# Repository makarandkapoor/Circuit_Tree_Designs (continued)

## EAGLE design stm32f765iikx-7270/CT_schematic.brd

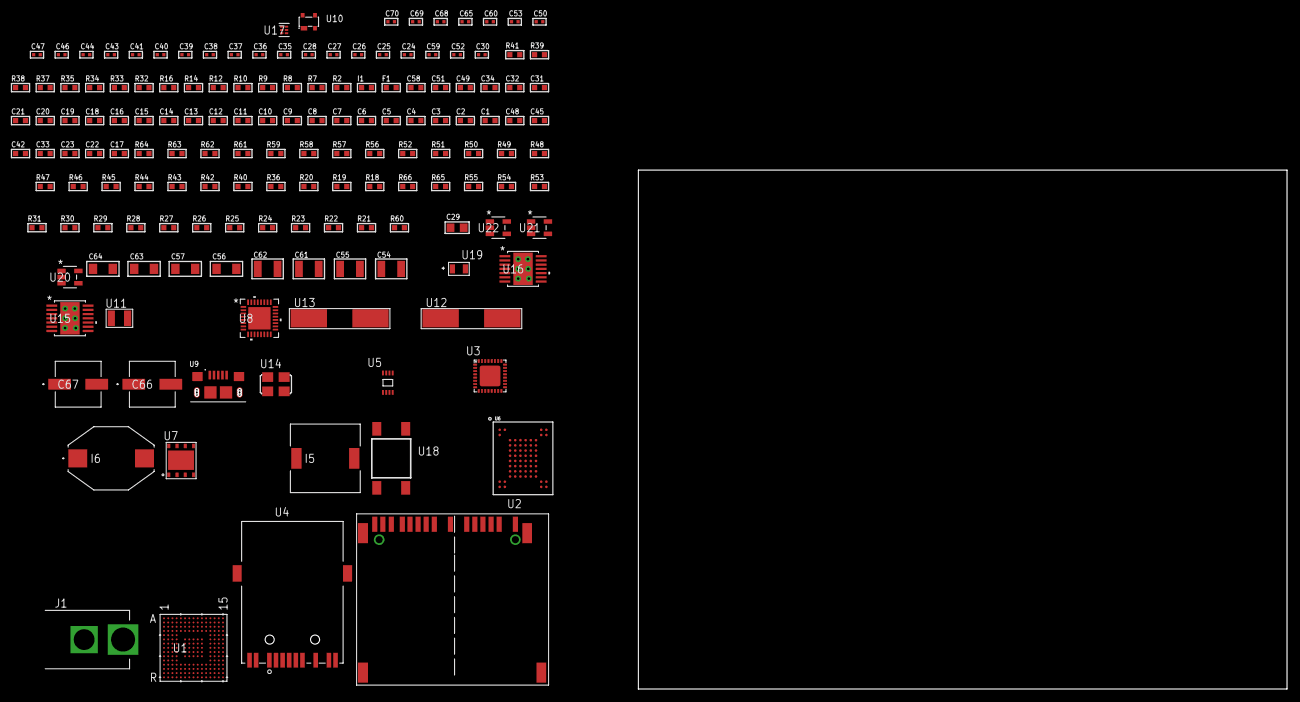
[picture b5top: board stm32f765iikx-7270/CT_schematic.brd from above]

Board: 2 copper layers, 154 parts (0 on the bottom side), 120 nets, no tracks yet.

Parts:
C1, C19, C31, C32, C34, C49, C51, C58: 1e-06; C0603
C2, C3, C4, C5, C6, C7, C8, C9, C10, C11, C12, C13, C14, C15, C16, C20, C21: 1e-07; C0603
C17: 4.7e-06; C0603
C18: 1e-08; C0603
C22, C23, C42, C45, C48: 2.2e-06; C0603
C24, C25, C26, C27, C35, C36: 1e-11; C0402
C28, C38, C39, C40, C41, C43, C44, C46, C47, C53, C60, C65: 1e-07; C0402
C29: 1e-05; C0805
C30: 2.2e-08; C0402
C33: 4.7e-10; C0603
C37, C50, C68, C69, C70: 1e-08; C0402
C52, C59: 3.3e-09; C0402
C54, C55, C61, C62: 2.2e-05; C1210
C56, C57, C63, C64: 1e-05; C1206
C66, C67: 0.0001; EXV-9H
F1: 240.0; L0603
I1: 97.0; R0603
I5: 3.8e-06; DR1040
I6: 1e-05; IND_PM3316
J1: PJ-037B; PJ-037B_PACKAGE
R2: 1000.0; R0603
R7, R8, R9: 4700.0; R0603
R10, R12, R14, R16: 2200.0; R0603
R18, R19, R20, R40, R42, R43, R44, R45, R46, R47, R48, R49, R50, R51, R52, R56, R57, R62, R63: 10000.0; R0603
R21, R22, R23, R24, R25, R26, R27, R28, R29, R30, R31, R53, R54, R55: 100000.0; R0603
R32, R33: 0.1; R0603
R34, R35: 200.0; R0603
R36: 12100.0; R0603
R37, R38, R39, R41: 49.9; R0603
R58: 30000.0; R0603
R59, R61: 22000.0; R0603
R60: 71007.101651032; R0603
R64: 82000.0; R0603
R65: 300000.0; R0603
R66: 120000.0; R0603
U1: STM32F765IIK6; UFBGA176_25
U2: 10100565
U3: LAN8710AI-EZK; QFN-32
U4: 7498011122R
U5: 24AA00T-I/MNY; TDFN-8/6MM
U6: mt29f4g08abbdah4; VFBGA-63
U7: SST26WF016B-104I/MF; WFDN-8
U8: TUSB1210BRHBR; RHB32_3P45X3P45
U9: 10118193-0001LF; FCI_10118193-0001LF
U10: prtr5v0u2ax; SOT143B
U11: ABS07-32.768KHZ-7-T
U12, U13: ABLS-25.000MHZ-B2F-T
U14: ASFL1-26MHZ-NCS; ASFL1
U15: tps54325PWP; HTSSOP14
U16: tps54225PWP; HTSSOP14
U17: TPS3895ADRYR; SON-6
U18: 4-1437565-2; SW_4-1437565-2
U19: Q65110A2395; LGM67K-G1J2-24-Z
U20, U21, U22: nc7sz125m5x; NC7SZ125M5X

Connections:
CLK_CRYSTAL_U1_E1: C24.1, U1.E1, U11.1
CLK_CRYSTAL_U1_F1: C25.1, U1.F1, U11.2
CLK_CRYSTAL_U1_G1: C26.1, U1.G1, U12.1
CLK_CRYSTAL_U1_H1: C27.1, U1.H1, U12.2
CLK_CRYSTAL_U3_4: C36.1, U3.4, U13.2
CLK_CRYSTAL_U3_5: C35.1, U3.5, U13.1
CLK_U8_1: U8.1, U14.3
GND: C1.2, C2.2, C3.2, C4.2, C5.2, C6.2, C7.2, C8.2, C9.2, C10.2, C11.2, C12.2, C13.2, C14.2, C15.2, C16.2, C17.2, C18.2, C19.2, C20.2, C21.2, C22.2, C23.2, C24.2, C25.2, C26.2, C27.2, C28.2, C29.2, C30.2, C31.2, C32.2, C33.2, C34.2, C35.2, C36.2, C37.2, C38.2, C39.2, C40.2, C41.2, C42.2, C43.2, C44.2, C45.2, C46.2, C47.2, C48.2, C49.2, C50.2, C51.2, C52.2, C54.2, C55.2, C56.2, C57.2, C58.2, C59.2, C61.2, C62.2, C63.2, C64.2, C65.2, C66.2, C67.2, C68.2, C69.2, C70.2, J1.2, R2.2, R18.2, R20.2, R32.2, R33.2, R34.2, R36.2, R47.2, R59.2, R61.2, R64.2, R66.2, U1.D5, U1.D7, U1.D8, U1.D9, U1.F2, U1.F6, U1.F7, U1.F8, U1.F9, U1.F10, U1.F12, U1.G2, U1.G6, U1.G7, U1.G8, U1.G9, U1.G10, U1.G12, U1.H6, U1.H7, U1.H8, U1.H9, U1.H10, U1.H12, U1.J6, U1.J7, U1.J8, U1.J9, U1.J10, U1.K6, U1.K7, U1.K8, U1.K9, U1.K10, U1.M1, U1.M8, U1.M9, U1.N1, U2.6, U2.10, U2.12, U2.16, U2.17, U2.20, U2.21, U3.EXP, U4.10, U5.4, U6.C5, U6.F7, U6.K3, U6.K8, U7.4, U7.9, U8.33, U9.5, U9.6, U9.7, U9.8, U9.9, U10.1, U14.2, U15.5, U15.8, U15.9, U15.15, U16.5, U16.8, U16.9, U16.15, U17.2, U19.C, U20.1, U20.3, U21.1, U21.3, U22.1, U22.3
NET_U1_C6: R19.1, U1.C6
NET_U1_D6: R18.1, U1.D6
NET_U1_E2: R12.1, U1.E2, U5.5
NET_U1_F13: C23.1, U1.F13
NET_U1_H3: R10.1, U1.H3, U5.6
NET_U1_J1: R8.1, U1.J1, U21.4
NET_U1_L4: R20.1, U1.L4
NET_U1_M3: R14.1, U1.M3, U3.17
NET_U1_M10: C22.1, U1.M10
NET_U1_P2: R16.1, U1.P2, U3.16
NET_U1_R1: C18.1, C19.1, F1.1, U1.P1, U1.R1
NET_U1_R15: U18.3, U18.4
NET_U2_1: R23.1, U2.1
NET_U2_2: R22.1, U2.2
NET_U2_18: U2.18, U2.19
NET_U3_1: C31.1, I1.1, R37.2, R38.2, R39.2, R41.2, U3.1, U3.27
NET_U3_6: C32.1, C33.1, U3.6
NET_U3_18: R40.1, U3.18
NET_U3_19: R7.1, U3.19, U20.4
NET_U3_32: R36.1, U3.32
NET_U4_1: R37.1, U3.29, U4.1
NET_U4_3: R35.2, R38.1, U3.28, U4.3
NET_U4_4: R39.1, U3.31, U4.4
NET_U4_5: C30.1, U4.2, U4.5
NET_U4_6: R41.1, U3.30, U4.6
NET_U4_8: R33.1, U4.8
NET_U4_9: R35.1, U4.9
NET_U4_11: U3.2, U4.11
NET_U4_12: R34.1, U4.12
NET_U4_13: R32.1, U4.13, U4.14
NET_U6_C3: R52.1, U6.C3
NET_U8_11: R56.1, U8.11
NET_U8_12: C48.1, U8.12
NET_U8_14: R57.1, U8.14
NET_U8_20: C45.1, U8.20
NET_U8_27: R9.1, U8.27, U22.4
NET_U9_1: C49.1, U8.22, U9.1, U10.4
NET_U9_2: U8.19, U9.2, U10.3
NET_U9_3: U8.18, U9.3, U10.2
NET_U15_2: R58.2, R59.1, U15.2
NET_U15_3: C51.1, U15.3
NET_U15_4: C52.1, U15.4
NET_U15_10: C53.1, I5.1, U15.10, U15.11
NET_U15_12: C53.2, U15.12
NET_U16_2: R60.2, R61.1, U16.2
NET_U16_3: C58.1, U16.3
NET_U16_4: C59.1, U16.4
NET_U16_10: C60.1, I6.1, U16.10, U16.11
NET_U16_12: C60.2, U16.12
NET_U17_1: R63.1, R64.1, U17.1
NET_U17_3: R65.2, R66.1, U17.3
NET_U17_4: R62.1, U17.4, U20.2, U21.2, U22.2
NET_U18_1: R2.1, U18.1, U18.2
PROC_ETH_COL: R44.1, U1.G4, U3.15
PROC_ETH_CRS: U1.F4, U3.14
PROC_ETH_RXD0: R42.1, U1.N5, U3.11
PROC_ETH_RXD1: R43.1, U1.P5, U3.10
PROC_ETH_RXD2: U1.M11, U3.9
PROC_ETH_RXD3: R47.1, U1.N12, U3.8
PROC_ETH_RX_CLK: R46.1, U1.N2, U3.7
PROC_ETH_RX_DV: U1.R3, U3.26
PROC_ETH_RX_ER: R45.1, U1.E3, U3.13
PROC_ETH_TXD0: U1.A8, U3.22
PROC_ETH_TXD1: U1.A7, U3.23
PROC_ETH_TXD2: U1.M4, U3.24
PROC_ETH_TXD3: U1.A2, U3.25
PROC_ETH_TX_CLK: U1.M5, U3.20
PROC_ETH_TX_EN: U1.B9, U3.21
PROC_FMC_A16: U1.N14, U6.D5
PROC_FMC_A17: U1.N13, U6.C4
PROC_FMC_D0: U1.M14, U6.H4
PROC_FMC_D1: U1.L14, U6.J4
PROC_FMC_D2: U1.B12, U6.K4
PROC_FMC_D3: U1.C12, U6.K5
PROC_FMC_D4: U1.R8, U6.K6
PROC_FMC_D5: U1.P8, U6.J7
PROC_FMC_D6: U1.P9, U6.K7
PROC_FMC_D7: U1.R9, U6.J8
PROC_FMC_INT: R48.1, U1.J14, U6.C8
PROC_FMC_NCE: R49.1, U1.C10, U6.C6
PROC_FMC_NOE: R51.1, U1.D10, U6.D4
PROC_FMC_NWE: R50.1, U1.C11, U6.C7
PROC_QUADSPI_BK1_IO0: U1.L3, U7.5
PROC_QUADSPI_BK1_IO1: U1.L2, U7.2
PROC_QUADSPI_BK1_IO2: R54.1, U1.K1, U7.3
PROC_QUADSPI_BK1_IO3: R55.1, U1.K2, U7.7
PROC_QUADSPI_BK1_NCS: R53.1, U1.B6, U7.1
PROC_QUADSPI_CLK: U1.L1, U7.6
PROC_SDMMC1_CK: R21.1, U1.A12, U2.8
PROC_SDMMC1_D0: R24.1, U1.G14, U2.4
PROC_SDMMC1_D1: R25.1, U1.F14, U2.3
PROC_SDMMC1_D2: R26.1, U1.B14, U2.15
PROC_SDMMC1_D3: R27.1, U1.B13, U2.14
PROC_SDMMC1_D4: R28.1, U1.A5, U2.13
PROC_SDMMC1_D5: R29.1, U1.B4, U2.11
PROC_SDMMC1_D6: R30.1, U1.H15, U2.7
PROC_SDMMC1_D7: R31.1, U1.G15, U2.5
PROC_USB_OTG_HS_ULPI_CK: U1.P4, U8.26
PROC_USB_OTG_HS_ULPI_D0: U1.R2, U8.3
PROC_USB_OTG_HS_ULPI_D1: U1.R5, U8.4
PROC_USB_OTG_HS_ULPI_D2: U1.R4, U8.5
PROC_USB_OTG_HS_ULPI_D3: U1.R12, U8.6
PROC_USB_OTG_HS_ULPI_D4: U1.R13, U8.7
PROC_USB_OTG_HS_ULPI_D5: U1.P12, U8.9
PROC_USB_OTG_HS_ULPI_D6: U1.P13, U8.10
PROC_USB_OTG_HS_ULPI_D7: U1.A6, U8.13
PROC_USB_OTG_HS_ULPI_DIR: U1.E4, U8.31
PROC_USB_OTG_HS_ULPI_NXT: U1.H4, U8.2
PROC_USB_OTG_HS_ULPI_STP: U1.M2, U8.29
VCC_S1_15V2: C56.1, C57.1, C63.1, C64.1, C66.1, C67.1, J1.1, U15.7, U15.13, U15.14, U16.7, U16.13, U16.14
VCC_TIER1_1V8: C1.1, C2.1, C3.1, C4.1, C5.1, C6.1, C7.1, C8.1, C9.1, C10.1, C11.1, C12.1, C13.1, C14.1, C15.1, C16.1, C17.1, C21.1, C28.1, C29.1, C34.1, C37.1, C38.1, C39.1, C40.1, C41.1, C42.1, C43.1, C46.1, C47.1, C54.1, C55.1, C65.1, C68.1, C69.1, C70.1, F1.2, I5.2, R7.2, R8.2, R9.2, R10.2, R12.2, R14.2, R16.2, R19.2, R21.2, R22.2, R23.2, R24.2, R25.2, R26.2, R27.2, R28.2, R29.2, R30.2, R31.2, R40.2, R42.2, R43.2, R44.2, R45.2, R46.2, R48.2, R49.2, R50.2, R51.2, R52.2, R53.2, R54.2, R55.2, R56.2, R57.2, R58.1, R62.2, R63.2, R65.1, U1.C1, U1.C5, U1.C7, U1.C8, U1.C9, U1.F3, U1.G3, U1.G13, U1.J12, U1.J13, U1.K4, U1.N8, U1.N9, U1.N10, U2.9, U3.12, U5.8, U6.D3, U6.G4, U6.H8, U6.J6, U7.8, U8.28, U8.30, U8.32, U15.1, U17.6, U20.5, U21.5, U22.5
VCC_TIER1_3V3: C20.1, C44.1, C50.1, C61.1, C62.1, I1.2, I6.2, R60.1, U1.H13, U8.21, U14.4, U16.1

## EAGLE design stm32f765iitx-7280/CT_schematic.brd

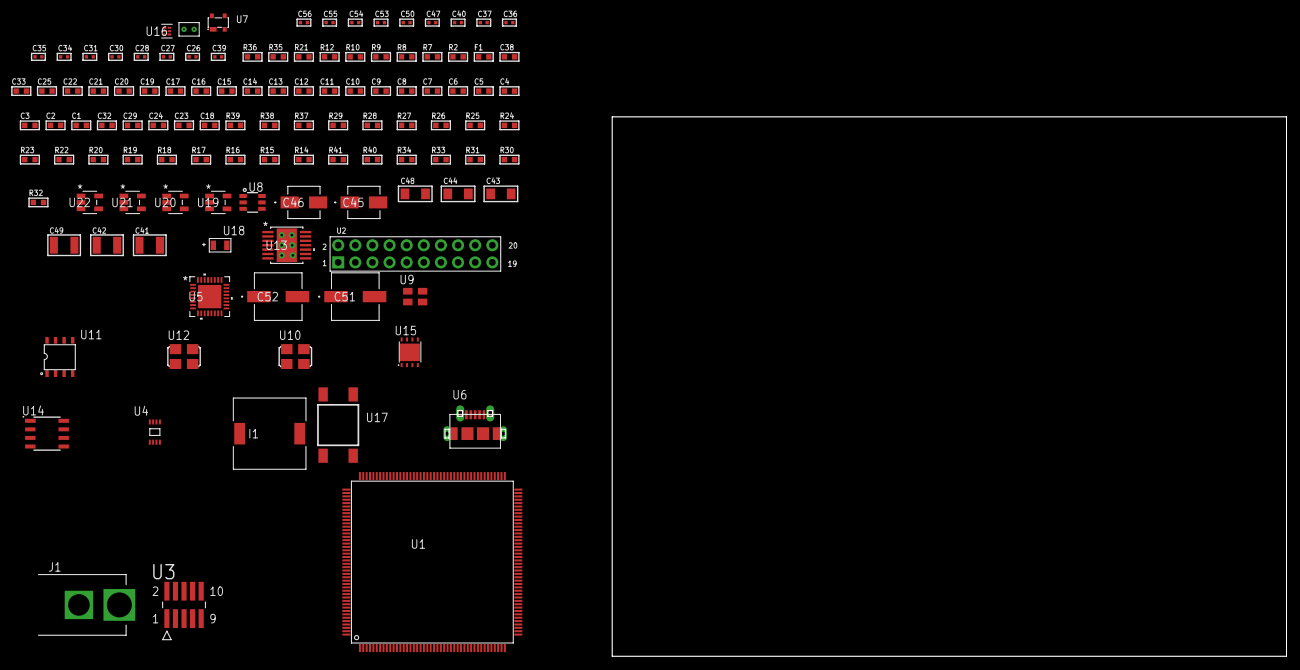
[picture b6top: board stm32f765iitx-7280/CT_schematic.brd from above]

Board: 2 copper layers, 124.8 x 80.0 mm, 116 parts (0 on the bottom side), 57 nets, no tracks yet.

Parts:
C1, C20, C25, C33, C38: 1e-06; C0603
C2, C3, C4, C5, C6, C7, C8, C9, C10, C11, C12, C13, C14, C15, C16, C17, C21, C22: 1e-07; C0603
C18: 4.7e-06; C0603
C19: 1e-08; C0603
C23, C24, C29, C32: 2.2e-06; C0603
C26, C28, C30, C31, C40, C50: 1e-07; C0402
C27, C34, C35, C36, C37, C47, C53, C54, C55, C56: 1e-08; C0402
C39: 3.3e-09; C0402
C41, C42: 2.2e-05; C1210
C43, C44, C48: 1e-05; C1206
C45: 1e-06; EXV-9B
C46: 2.2e-06; EXV-9B
C49: 1e-05; C1210
C51, C52: 0.0001; EXV-9H
F1: 240.0; L0603
I1: 5.2e-06; DR1040
J1: PJ-037B; PJ-037B_PACKAGE
R2, R36: 1000.0; R0603
R7, R8, R9: 4700.0; R0603
R10, R12: 2200.0; R0603
R14, R15, R16, R17, R18, R19, R20, R22, R23, R24, R26, R27, R37, R38: 10000.0; R0603
R21: 5.0; R0603
R25: 47000.0; R0603
R28: 30000.0; R0603
R29: 22000.0; R0603
R30, R31, R33, R34: 100000.0; R0603
R32: 164658.62; R0603
R35: 3900.0; R0603
R39: 82000.0; R0603
R40: 300000.0; R0603
R41: 120000.0; R0603
U1: STM32F765IIT6; LQFP176
U2: arducam_ov2640; ARDUCAM
U3: FTSH-105-01-L-DV-K; SAMTEC_FTSH-105-01-L-DV-K
U4: 24AA128T-I/MNY; TDFN-8/6MM
U5: TUSB1210BRHBR; RHB32_3P45X3P45
U6: 47590-0001; MICRO_USB_AB
U7: prtr5v0u2ax; SOT143B
U8: MAX4995AAUT+T; SOT-23-6
U9: ASEK-32.768KHz-ECST; ASEK
U10: ASFL1-25MHZ-NCS; ASFL1
U11: idt74fct38072; IDT74FCT38072
U12: ASFL1-26MHZ-NCS; ASFL1
U13: tps54225PWP; HTSSOP14
U14: LP2954AIMX/NOPB; LP2954
U15: LP3878SDX-ADJ/NOPB; WSON-8
U16: TPS3895ADRYR; SON-6
U17: 4-1437565-2; SW_4-1437565-2
U18: Q65110A2395; LGM67K-G1J2-24-Z
U19, U20, U21, U22: nc7sz125m5x; NC7SZ125M5X
U23: Dummy; DUMMY_PACKAGE_251

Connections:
CLK_U1_9: U1.9, U9.3
CLK_U1_29: U1.29, U11.6
CLK_U2_8: U2.8, U11.7
CLK_U5_1: U5.1, U12.3
CLK_U11_3: U10.3, U11.3
GND: C1.2, C2.2, C3.2, C4.2, C5.2, C6.2, C7.2, C8.2, C9.2, C10.2, C11.2, C12.2, C13.2, C14.2, C15.2, C16.2, C17.2, C18.2, C19.2, C20.2, C21.2, C22.2, C23.2, C24.2, C25.2, C26.2, C27.2, C28.2, C29.2, C30.2, C31.2, C32.2, C33.2, C34.2, C35.2, C36.2, C37.2, C38.2, C39.2, C41.2, C42.2, C43.2, C44.2, C45.2, C46.2, C47.2, C48.2, C49.2, C50.2, C51.2, C52.2, C53.2, C54.2, C55.2, C56.2, J1.2, R2.2, R14.2, R16.2, R20.2, R21.2, R22.2, R23.2, R25.2, R29.2, R33.2, R36.2, R39.2, R41.2, U1.14, U1.22, U1.37, U1.61, U1.71, U1.90, U1.102, U1.113, U1.126, U1.135, U1.148, U1.158, U2.2, U2.20, U3.3, U3.5, U4.4, U4.7, U5.33, U6.5, U6.6, U6.7, U6.8, U6.9, U7.1, U8.2, U9.2, U10.2, U11.4, U11.5, U11.8, U12.2, U13.5, U13.8, U13.9, U13.15, U14.4, U15.3, U15.PAD, U16.2, U18.C, U19.2, U19.3, U20.1, U20.3, U21.1, U21.3, U22.1, U22.3, U23.1
NET_U1_31: R7.1, U1.31, U20.4
NET_U1_39: C19.1, C20.1, F1.1, U1.38, U1.39
NET_U1_48: R16.1, U1.48
NET_U1_81: C23.1, U1.81
NET_U1_125: C24.1, U1.125
NET_U1_164: R10.1, U1.164, U4.6
NET_U1_165: R12.1, U1.165, U4.5
NET_U1_166: R14.1, U1.166
NET_U1_171: R15.1, U1.171
NET_U1_176: U17.3, U17.4
NET_U2_19: R8.1, U2.19, U21.4
NET_U3_9: R21.1, U3.9
NET_U4_1: R22.1, U4.1
NET_U4_2: R23.1, U4.2
NET_U4_3: R24.1, U4.3
NET_U5_11: R26.1, U5.11
NET_U5_12: C32.1, U5.12
NET_U5_14: R27.1, U5.14
NET_U5_20: C29.1, U5.20
NET_U5_27: R9.1, U5.27, U22.4
NET_U6_1: C33.1, U5.22, U6.1, U7.4, U8.1
NET_U6_2: U5.19, U6.2, U7.3
NET_U6_3: U5.18, U6.3, U7.2
NET_U6_4: U5.23, U6.4
NET_U8_3: R25.1, U8.3
NET_U8_4: U5.17, U8.4
NET_U13_2: R28.2, R29.1, U13.2
NET_U13_3: C38.1, U13.3
NET_U13_4: C39.1, U13.4
NET_U13_10: C40.1, I1.1, U13.10, U13.11
NET_U13_12: C40.2, U13.12
NET_U14_3: R31.1, U14.3
NET_U14_5: R30.1, U14.5
NET_U14_7: R32.2, R33.1, U14.7
NET_U15_1: C47.1, U15.1
NET_U15_6: R35.2, R36.1, U15.6
NET_U15_8: R34.1, U15.8
NET_U16_1: R38.1, R39.1, U16.1
NET_U16_3: R40.2, R41.1, U16.3
NET_U16_4: R37.1, U16.4, U19.4, U20.2, U21.2, U22.2
NET_U17_1: R2.1, U17.1, U17.2
PROC_DAC_OUT1: U1.50, U23.2
PROC_SYS_JTCK_SWCLK: R20.1, U1.137, U3.4
PROC_SYS_JTDI: R18.1, U1.138, U3.8
PROC_SYS_JTDO_SWO: U1.161, U3.6
PROC_SYS_JTMS_SWDIO: R19.1, U1.124, U3.2
RST_OUT_U3_JTAG_RST_B: R17.1, U3.10, U19.1
VCC_S1_8V1: C43.1, C44.1, C45.1, C48.1, C51.1, C52.1, J1.1, R31.2, R34.2, U13.7, U13.13, U13.14, U14.8, U15.4
VCC_TIER1_1V8: C1.1, C2.1, C3.1, C4.1, C5.1, C6.1, C7.1, C8.1, C9.1, C10.1, C11.1, C12.1, C13.1, C14.1, C15.1, C16.1, C17.1, C18.1, C22.1, C26.1, C27.1, C30.1, C31.1, C41.1, C42.1, C50.1, C53.1, C54.1, C55.1, C56.1, F1.2, I1.2, R7.2, R9.2, R10.2, R12.2, R15.2, R17.2, R18.2, R19.2, R24.2, R26.2, R27.2, R28.1, R37.2, R38.2, R40.1, U1.6, U1.15, U1.23, U1.36, U1.49, U1.62, U1.72, U1.82, U1.91, U1.103, U1.127, U1.136, U1.149, U1.159, U1.172, U3.1, U4.8, U5.28, U5.30, U5.32, U13.1, U16.6, U19.5, U20.5, U21.5, U22.5
VCC_TIER1_3V3: C21.1, C25.1, C28.1, C34.1, C35.1, C36.1, C37.1, C46.1, R8.2, R30.2, R32.1, U1.114, U2.1, U5.21, U9.4, U10.4, U11.1, U11.2, U12.4, U14.1
VCC_TIER1_5V0: C49.1, R35.1, U8.5, U15.5

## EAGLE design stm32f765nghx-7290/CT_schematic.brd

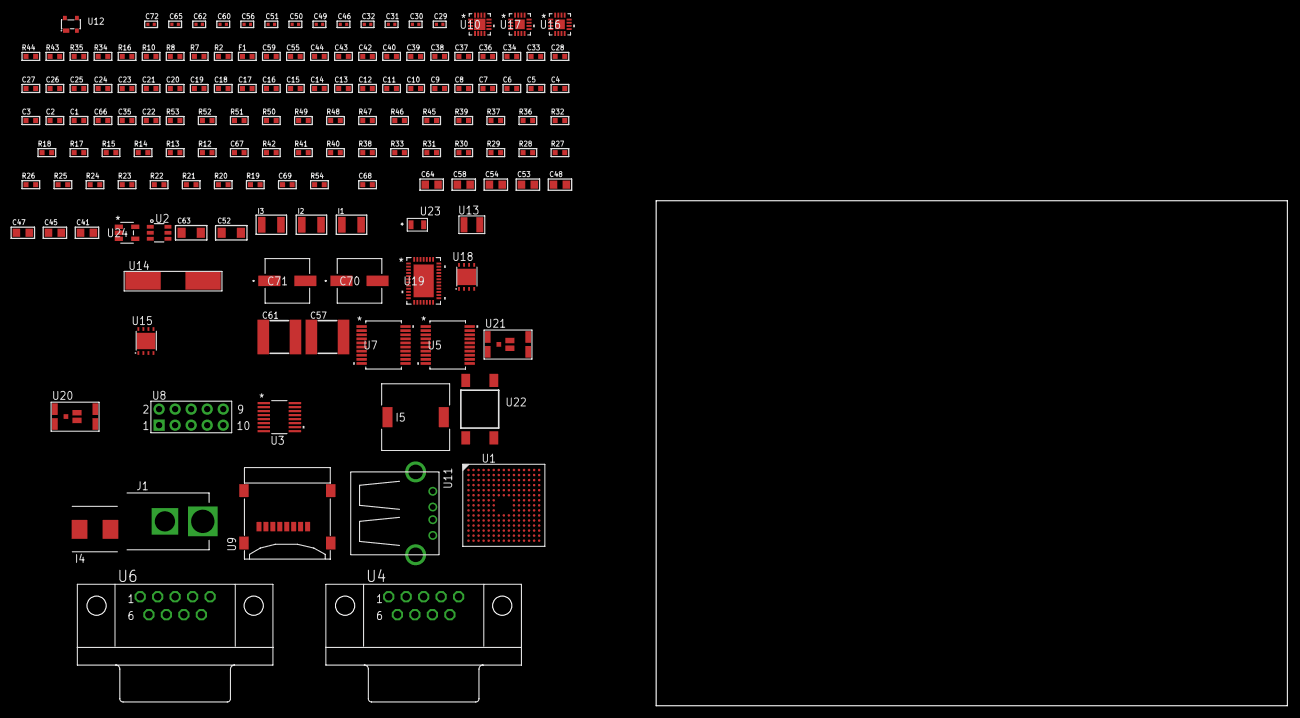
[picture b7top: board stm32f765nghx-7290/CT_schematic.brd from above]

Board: 2 copper layers, 100.0 x 80.0 mm, 150 parts (0 on the bottom side), 113 nets, no tracks yet.

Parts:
C1, C24, C33, C34, C36, C37, C38, C39, C40, C42, C43, C44, C55, C59: 1e-06; C0603
C2, C3, C4, C5, C6, C7, C8, C9, C10, C11, C12, C13, C14, C15, C16, C17, C18, C19, C20, C21, C25, C26, C27, C28: 1e-07; C0603
C22: 4.7e-06; C0603
C23: 1e-08; C0603
C29, C30, C31, C32: 1e-11; C0402
C35: 2.2e-07; C0603
C41, C45, C48: 4.7e-06; C0805
C46, C49, C50, C56, C60, C65: 1e-07; C0402
C47, C53, C54, C58, C64: 1e-05; C0805
C51, C62, C72: 1e-08; C0402
C52, C63: 1e-05; C1206
C57, C61: 6.8e-05; 2220
C66: 2.2e-06; C0603
C67: 2.45e-08; R0603
C68: 2.8258362168397e-09; R0603
C69: 7.105e-09; R0603
C70, C71: 0.0001; EXV-9H
F1: 240.0; L0603
I1: 1e-05; L1210
I2, I3: 1.5e-05; L1210
I4: 3.3e-06; WE-HCI_7030/7040/7050
I5: 3.8e-06; DR1040
J1: PJ-037B; PJ-037B_PACKAGE
R2, R35, R44: 1000.0; R0603
R7: 4700.0; R0603
R8, R10: 2200.0; R0603
R12: 47000.0; R0603
R13, R14, R15, R17, R18, R32, R45, R47, R48, R51, R52, R53: 10000.0; R0603
R16: 1270.0; R0603
R19, R20, R21, R22, R23, R24, R25, R26, R27, R28, R29, R30, R31, R33, R42: 100000.0; R0603
R34, R43: 200.0; R0603
R36, R39: 20000.0; R0603
R37: 62000.0; R0603
R38, R41: 300000.0; R0603
R40: 150000.0; R0603
R46: 75000.0; R0603
R49, R50: 95300.0; R0603
R54: 44545.454545455; R0603
U1: STM32F765NGH6; TFBGA216
U2: MAX4995AAUT+T; SOT-23-6
U3: LTC2804CGN-1#PBF; SSOP-16
U4, U6: 182-009-113R531; 182-009-MALE
U5, U7: MAX3218EAP+T; SSOP-20
U8: HTSS-105-01-G-D
U9: 0472192001; MOLEX_47219-2001
U10: MMA8451QT; QFN-16
U11: 61400416021; USB-A-H
U12: prtr5v0u2ax; SOT143B
U13: ABS07-32.768KHZ-7-T
U14: ABLS-25.000MHZ-B2F-T
U15, U18: LP3878SDX-ADJ/NOPB; WSON-8
U16, U17: LTC3601EUD#PBF; QFN-16_EP
U19: LTC2928CUHF#PBF; QFN-38_UHF
U20, U21: IRF8306MTRPbF; IRF8306MTRPBF
U22: 4-1437565-2; SW_4-1437565-2
U23: Q65110A2395; LGM67K-G1J2-24-Z
U24: nc7sz125m5x; NC7SZ125M5X

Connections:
CLK_CRYSTAL_U1_E1: C29.1, U1.E1, U13.1
CLK_CRYSTAL_U1_F1: C30.1, U1.F1, U13.2
CLK_CRYSTAL_U1_G1: C31.1, U1.G1, U14.1
CLK_CRYSTAL_U1_H1: C32.1, U1.H1, U14.2
GND: C1.2, C2.2, C3.2, C4.2, C5.2, C6.2, C7.2, C8.2, C9.2, C10.2, C11.2, C12.2, C13.2, C14.2, C15.2, C16.2, C17.2, C18.2, C19.2, C20.2, C21.2, C22.2, C23.2, C24.2, C25.2, C26.2, C27.2, C28.2, C29.2, C30.2, C31.2, C32.2, C33.2, C34.2, C36.2, C37.2, C38.2, C39.2, C40.2, C42.2, C43.2, C44.2, C46.2, C47.2, C48.2, C49.2, C50.2, C51.2, C52.2, C53.2, C54.2, C55.2, C57.1, C57.2, C58.2, C59.2, C61.1, C61.2, C62.2, C63.2, C64.2, C65.2, C66.2, C67.2, C68.2, C69.2, C70.2, C71.2, C72.2, J1.2, R2.2, R12.2, R13.2, R16.2, R18.2, R32.2, R35.2, R36.2, R38.2, R39.2, R41.2, R44.2, R46.2, R49.2, R50.2, R51.2, R52.2, R53.2, U1.F2, U1.F6, U1.F7, U1.F8, U1.F9, U1.F10, U1.G6, U1.G10, U1.H6, U1.H10, U1.J6, U1.J10, U1.K6, U1.K7, U1.K8, U1.K9, U1.K10, U1.L6, U1.M1, U1.N1, U2.2, U3.8, U4.5, U5.5, U5.17, U5.20, U6.5, U7.5, U7.17, U7.20, U8.9, U9.6, U9.G1, U9.G2, U9.G3, U9.G4, U10.5, U10.10, U10.12, U10.17, U11.4, U11.5, U11.6, U12.1, U15.3, U15.PAD, U16.1, U16.9, U16.17, U17.1, U17.9, U17.17, U18.3, U18.PAD, U19.8, U19.9, U19.10, U19.12, U19.13, U19.24, U19.25, U19.30, U19.32, U19.39, U23.C, U24.1, U24.3
NET_U1_A7: R8.1, U1.A7, U10.4
NET_U1_B4: R10.1, U1.B4, U10.6
NET_U1_D15: R16.1, U1.D15
NET_U1_E5: R14.1, U1.E5
NET_U1_E6: R13.1, U1.E6
NET_U1_E11: C28.1, U1.E11
NET_U1_J1: R7.1, U1.J1, U24.4
NET_U1_L5: R15.1, U1.L5
NET_U1_R1: C23.1, C24.1, F1.1, U1.P1, U1.R1
NET_U1_R15: U22.3, U22.4
NET_U2_3: R12.1, U2.3
NET_U3_6: C33.1, U3.6
NET_U3_7: C35.1, I1.2, U3.7
NET_U3_9: C34.1, U3.9
NET_U3_10: C35.2, U3.10
NET_U3_11: R19.1, U3.11
NET_U4_2: U3.1, U4.2
NET_U4_3: U3.3, U4.3
NET_U4_7: U3.2, U4.7
NET_U4_8: U3.4, U4.8
NET_U5_1: I2.1, U5.1
NET_U5_2: R20.1, U5.2
NET_U5_3: R21.1, U5.3
NET_U5_4: R22.1, U5.4
NET_U5_15: C40.1, U5.15
NET_U5_16: C41.2, U5.16
NET_U5_18: C41.1, U5.18
NET_U5_19: C39.1, U5.19
NET_U6_2: U5.12, U6.2
NET_U6_3: U5.14, U6.3
NET_U6_7: U5.11, U6.7
NET_U6_8: U5.13, U6.8
NET_U7_1: I3.1, U7.1
NET_U7_2: R23.1, U7.2
NET_U7_3: R24.1, U7.3
NET_U7_4: R25.1, U7.4
NET_U7_15: C44.1, U7.15
NET_U7_16: C45.2, U7.16
NET_U7_18: C45.1, U7.18
NET_U7_19: C43.1, U7.19
NET_U8_3: U7.12, U8.3
NET_U8_4: U7.11, U8.4
NET_U8_5: U7.14, U8.5
NET_U8_6: U7.13, U8.6
NET_U10_2: C50.1, U10.2
NET_U10_7: R32.1, U10.7
NET_U15_1: C51.1, U15.1
NET_U15_6: R34.2, R35.1, U15.6
NET_U15_8: R33.1, U15.8
NET_U16_3: C56.2, I4.1, U16.3, U16.4
NET_U16_6: C56.1, U16.6
NET_U16_7: C55.1, U16.7, U16.12
NET_U16_10: R38.1, U16.10
NET_U16_11: R36.1, R37.1, U16.11
NET_U16_ATNET_3: I4.2, R37.2
NET_U17_3: C60.2, I5.1, U17.3, U17.4
NET_U17_6: C60.1, U17.6
NET_U17_7: C59.1, U17.7, U17.12
NET_U17_10: R41.1, U17.10
NET_U17_11: R39.1, R40.1, U17.11
NET_U17_ATNET_3: I5.2, R40.2
NET_U18_1: C62.1, U18.1
NET_U18_6: R43.2, R44.1, U18.6
NET_U18_8: R42.1, U18.8
NET_U19_3: R52.1, U19.3
NET_U19_6: R49.1, U19.6
NET_U19_7: R50.1, U19.7
NET_U19_16: R51.1, R54.1, U19.16
NET_U19_18: R48.1, U19.18
NET_U19_19: R47.1, U19.19, U19.20
NET_U19_21: R45.1, R46.1, U19.21, U24.2
NET_U19_26: C68.1, U19.26
NET_U19_27: C67.1, U19.27
NET_U19_28: C69.1, U19.28
NET_U19_38: R53.1, U19.38
NET_U20_3: U19.2, U20.3
NET_U21_3: U19.37, U21.3
NET_U22_1: R2.1, U22.1, U22.2
PROC_GPIO_TO_U1_USB_FAULT: R17.1, U1.A2, U2.6
PROC_GPIO_TO_U1_VBUS_EN: R18.1, U1.A1, U2.4
PROC_SDMMC2_CK: R27.1, U1.B11, U9.5
PROC_SDMMC2_CMD: R26.1, U1.A11, U9.3
PROC_SDMMC2_D0: R28.1, U1.D9, U9.7
PROC_SDMMC2_D1: R29.1, U1.C8, U9.8
PROC_SDMMC2_D2: R30.1, U1.A10, U9.1
PROC_SDMMC2_D3: R31.1, U1.A9, U9.2
PROC_UART4_CTS: U1.R5, U5.8
PROC_UART4_RTS: U1.A13, U5.10
PROC_UART4_RX: U1.B12, U5.9
PROC_UART4_TX: U1.B14, U5.7
PROC_UART5_CTS: U1.F14, U7.8
PROC_UART5_RTS: U1.G14, U7.10
PROC_UART5_RX: U1.A8, U7.9
PROC_UART5_TX: U1.A12, U7.7
PROC_UART7_CTS: U1.L2, U3.13
PROC_UART7_RTS: U1.L3, U3.15
PROC_UART7_RX: U1.F15, U3.16
PROC_UART7_TX: U1.K1, U3.14
PROC_USB_OTG_FS_DM: U1.C15, U11.2, U12.3
PROC_USB_OTG_FS_DP: U1.B15, U11.3, U12.2
PROC_USB_OTG_FS_VBUS: U1.E15, U2.1, U11.1, U12.4
VCC_6V1: C65.1, C66.1, C70.1, C71.1, J1.1, R45.2, R47.2, R48.2, R54.2, U19.11, U19.22, U20.1, U20.2, U20.6, U20.7, U21.1, U21.2, U21.6, U21.7
VCC_S1_6V1: C52.1, C54.1, C58.1, R33.2, U15.4, U16.15, U16.16, U17.15, U17.16, U20.4, U20.5
VCC_S2_6V1: C63.1, R42.2, U18.4, U21.4, U21.5
VCC_TIER1_1V2: C27.1, C53.1, R34.1, U1.L11, U15.5
VCC_TIER1_2V5: C1.1, C2.1, C3.1, C4.1, C5.1, C6.1, C7.1, C8.1, C9.1, C10.1, C11.1, C12.1, C13.1, C14.1, C15.1, C16.1, C17.1, C18.1, C19.1, C20.1, C21.1, C22.1, C25.1, C26.1, C36.1, C37.1, C38.1, C42.1, C46.1, C47.1, C48.1, C49.1, C57.2, C72.1, F1.2, I1.1, I2.2, I3.2, I4.2, R7.2, R8.2, R10.2, R14.2, R15.2, R17.2, R19.2, R20.2, R21.2, R22.2, R23.2, R24.2, R25.2, R26.2, R27.2, R28.2, R29.2, R30.2, R31.2, R37.2, U1.C1, U1.E7, U1.E8, U1.E9, U1.E10, U1.F4, U1.F5, U1.F11, U1.G5, U1.G11, U1.H5, U1.H11, U1.J5, U1.J11, U1.K5, U1.K11, U1.L7, U1.L8, U1.L9, U1.L10, U3.5, U3.12, U5.6, U7.6, U9.4, U10.1, U10.14, U16.8, U24.5
VCC_TIER1_5V0: C61.2, I5.2, R40.2, U2.5, U17.8
VCC_TIER2_1V2: C64.1, R43.1, U18.5

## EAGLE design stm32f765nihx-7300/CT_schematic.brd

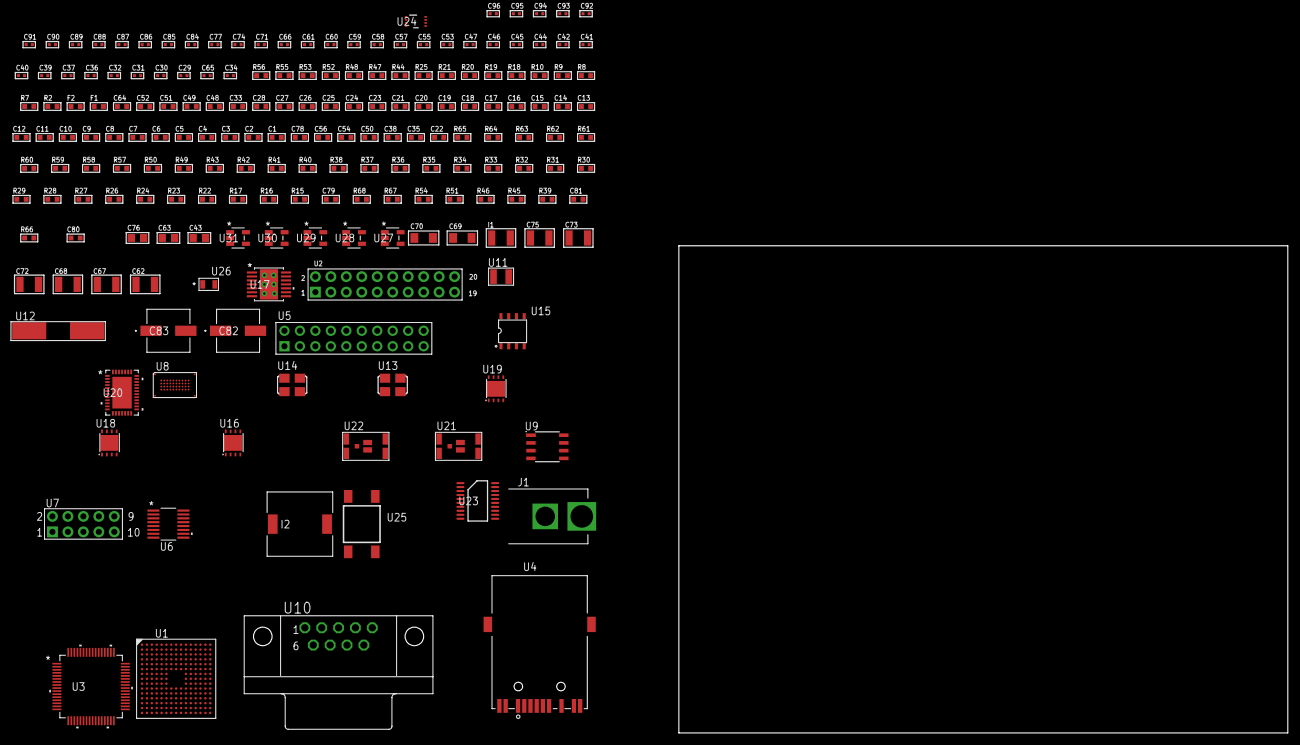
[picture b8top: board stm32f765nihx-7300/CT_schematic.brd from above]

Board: 2 copper layers, 100.0 x 80.0 mm, 191 parts (0 on the bottom side), 145 nets, no tracks yet.

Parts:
C1, C24, C33, C48, C49, C51, C52, C64: 1e-06; C0603
C2, C3, C4, C5, C6, C7, C8, C9, C10, C11, C12, C13, C14, C15, C16, C17, C18, C19, C20, C21, C25, C26, C27, C28: 1e-07; C0603
C22: 4.7e-06; C0603
C23: 1e-08; C0603
C29, C30, C31, C32: 1e-11; C0402
C34: 1.8e-08; C0402
C35, C38, C54, C56, C78: 2.2e-06; C0603
C36, C39, C41, C42, C44, C45, C46, C47, C53, C55, C57, C66, C77, C85, C87, C89, C91: 1e-07; C0402
C37, C40, C58, C59, C60, C61, C71, C74, C84, C86, C88, C90, C92, C93, C94, C95, C96: 1e-08; C0402
C43, C63, C76: 1e-05; C0805
C50: 2.2e-07; C0603
C62, C72, C73, C75: 1e-05; C1210
C65: 3.3e-09; C0402
C67, C68: 2.2e-05; C1210
C69, C70: 1e-05; C1206
C79: 2.45e-08; R0603
C80: 2.8258362168397e-09; R0603
C81: 7.105e-09; R0603
C82, C83: 0.0001; EXV-9H
F1: 240.0; L0603
F2: 510.0; L0603
I1: 1e-05; L1210
I2: 5.2e-06; DR1040
J1: PJ-037B; PJ-037B_PACKAGE
R2, R48, R53, R56: 1000.0; R0603
R7, R8, R9, R10: 4700.0; R0603
R15, R16, R17, R22, R23, R24, R26, R27, R28, R29, R30, R31, R32, R33, R34, R35, R36, R37, R38, R40, R41, R42, R43, R57, R59, R60, R63, R64, R65: 10000.0; R0603
R18, R19: 0.1; R0603
R20, R21, R47, R55: 200.0; R0603
R25: 1270.0; R0603
R39, R45, R46, R51, R54: 100000.0; R0603
R44: 120.0; R0603
R49: 30000.0; R0603
R50: 22000.0; R0603
R52: 2231.0; R0603
R58: 75000.0; R0603
R61, R62: 95300.0; R0603
R66: 122054.54545455; R0603
R67, R68: 200000.0; R0603
U1: STM32F765NIH6; TFBGA216
U2: arducam_ov2640; ARDUCAM
U3: BCM5221KPT; TQFP64_10X10MC
U4: 7498011122R
U5: TST-110-05-T-D-RA
U6: LTC2804CGN-1#PBF; SSOP-16
U7: HTSS-105-01-G-D
U8: S29VS256RABBHW000
U9: SN65HVD230D; SOIC-8
U10: 182-009-113R531; 182-009-MALE
U11: ABS07-32.768KHZ-7-T
U12: ABLS-25.000MHZ-B2F-T
U13: ASFL1-25MHZ-NCS; ASFL1
U14: ASFL1-50MHZ-NCS; ASFL1
U15: idt74fct38072; IDT74FCT38072
U16, U18, U19: LP3878SDX-ADJ/NOPB; WSON-8
U17: tps54225PWP; HTSSOP14
U20: LTC2928CUHF#PBF; QFN-38_UHF
U21, U22: IRF8306MTRPbF; IRF8306MTRPBF
U23: LSF0108PWR; PW0020A
U24: LSF0102DCTR; DCU0008A_N
U25: 4-1437565-2; SW_4-1437565-2
U26: Q65110A2395; LGM67K-G1J2-24-Z
U27, U28, U29, U30, U31: nc7sz125m5x; NC7SZ125M5X

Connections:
CLK_CRYSTAL_U1_E1: C29.1, U1.E1, U11.1
CLK_CRYSTAL_U1_F1: C30.1, U1.F1, U11.2
CLK_CRYSTAL_U1_G1: C31.1, U1.G1, U12.1
CLK_CRYSTAL_U1_H1: C32.1, U1.H1, U12.2
CLK_U1_N2: U1.N2, U15.7
CLK_U2_8: U2.8, U13.3
CLK_U3_4: U3.4, U15.6
CLK_U15_3: U14.3, U15.3
GND: C1.2, C2.2, C3.2, C4.2, C5.2, C6.2, C7.2, C8.2, C9.2, C10.2, C11.2, C12.2, C13.2, C14.2, C15.2, C16.2, C17.2, C18.2, C19.2, C20.2, C21.2, C22.2, C23.2, C24.2, C25.2, C26.2, C27.2, C28.2, C29.2, C30.2, C31.2, C32.2, C33.2, C34.2, C35.2, C36.2, C37.2, C38.2, C39.2, C40.2, C41.2, C42.2, C43.2, C44.2, C45.2, C46.2, C47.2, C48.2, C49.2, C51.2, C52.2, C53.2, C54.2, C55.2, C56.2, C57.2, C58.2, C59.2, C60.2, C61.2, C62.2, C63.2, C64.2, C65.2, C67.2, C68.2, C69.2, C70.2, C71.2, C72.2, C73.2, C74.2, C75.2, C76.2, C77.2, C78.2, C79.2, C80.2, C81.2, C82.2, C83.2, C84.2, C85.2, C86.2, C87.2, C88.2, C89.2, C90.2, C91.2, C92.2, C93.2, C94.2, C95.2, C96.2, J1.2, R2.2, R15.2, R18.2, R19.2, R22.2, R24.2, R25.2, R26.2, R28.2, R29.2, R30.2, R31.2, R32.2, R38.2, R45.2, R48.2, R50.2, R53.2, R56.2, R58.2, R61.2, R62.2, R63.2, R64.2, R65.2, U1.F2, U1.F6, U1.F7, U1.F8, U1.F9, U1.F10, U1.G6, U1.G10, U1.H6, U1.H10, U1.J6, U1.J10, U1.K6, U1.K7, U1.K8, U1.K9, U1.K10, U1.L6, U1.M1, U1.N1, U2.2, U2.20, U3.6, U3.7, U3.24, U3.29, U3.32, U3.40, U3.45, U3.54, U3.63, U4.10, U4.12, U5.4, U5.6, U5.8, U5.10, U5.12, U5.14, U5.16, U5.18, U5.20, U6.8, U7.9, U8.C5, U8.D12, U8.E3, U8.F5, U9.2, U10.5, U13.2, U14.2, U15.4, U15.5, U15.8, U16.3, U16.PAD, U17.5, U17.8, U17.9, U17.15, U18.3, U18.PAD, U19.3, U19.PAD, U20.8, U20.9, U20.10, U20.12, U20.13, U20.24, U20.25, U20.30, U20.32, U20.39, U23.1, U24.1, U26.C, U27.2, U27.3, U28.1, U28.3, U29.1, U29.3, U30.1, U30.3, U31.1, U31.3
NET_U1_E5: R16.1, U1.E5
NET_U1_E6: R15.1, U1.E6
NET_U1_E11: C28.1, U1.E11
NET_U1_J1: R9.1, U1.J1, U30.4
NET_U1_L5: R17.1, U1.L5
NET_U1_R1: C23.1, C24.1, F1.1, U1.P1, U1.R1
NET_U1_R15: U25.3, U25.4
NET_U2_19: R10.1, U2.19, U31.4
NET_U3_2: C38.1, C39.1, C40.1, U3.2, U3.55
NET_U3_9: R7.1, U3.9, U28.4
NET_U3_10: R26.1, U3.10
NET_U3_11: R27.1, U3.11
NET_U3_12: R28.1, U3.12
NET_U3_13: R29.1, U3.13
NET_U3_14: R30.1, U3.14
NET_U3_16: R24.1, U3.16
NET_U3_18: R32.1, U3.18
NET_U3_23: R25.1, U3.23
NET_U3_27: C35.1, C36.1, C37.1, U3.22, U3.27, U3.28
NET_U3_37: R31.1, U3.37
NET_U3_38: R22.1, U3.38
NET_U3_39: R23.1, U3.39
NET_U4_1: U3.31, U4.1
NET_U4_2: F2.2, U4.2
NET_U4_3: U3.30, U4.3
NET_U4_4: U3.26, U4.4
NET_U4_5: C34.1, F2.1, U4.2, U4.5
NET_U4_6: U3.25, U4.6
NET_U4_8: R19.1, U4.8
NET_U4_9: R20.1, U4.9
NET_U4_11: R21.1, U4.11
NET_U4_12: R20.2, U4.12
NET_U4_13: R18.1, U4.13, U4.14
NET_U5_19: R38.1, U5.19
NET_U6_6: C48.1, U6.6
NET_U6_7: C50.1, I1.2, U6.7
NET_U6_9: C49.1, U6.9
NET_U6_10: C50.2, U6.10
NET_U6_11: R39.1, U6.11
NET_U7_3: U6.1, U7.3
NET_U7_4: U6.2, U7.4
NET_U7_5: U6.3, U7.5
NET_U7_6: U6.4, U7.6
NET_U8_D8: R8.1, U8.D8, U29.4
NET_U9_6: R44.2, U9.6
NET_U9_8: R45.1, U9.8
NET_U10_2: R44.2, U9.6, U10.2
NET_U10_3: R44.1, U9.7, U10.3
NET_U16_1: C61.1, U16.1
NET_U16_6: R47.2, R48.1, U16.6
NET_U16_8: R46.1, U16.8
NET_U17_2: R49.2, R50.1, U17.2
NET_U17_3: C64.1, U17.3
NET_U17_4: C65.1, U17.4
NET_U17_10: C66.1, I2.1, U17.10, U17.11
NET_U17_12: C66.2, U17.12
NET_U18_1: C71.1, U18.1
NET_U18_6: R52.2, R53.1, U18.6
NET_U18_8: R51.1, U18.8
NET_U19_1: C74.1, U19.1
NET_U19_6: R55.2, R56.1, U19.6
NET_U19_8: R54.1, U19.8
NET_U20_3: R64.1, U20.3
NET_U20_6: R61.1, U20.6
NET_U20_7: R62.1, U20.7
NET_U20_16: R63.1, R66.1, U20.16
NET_U20_18: R60.1, U20.18
NET_U20_19: R59.1, U20.19, U20.20
NET_U20_21: R57.1, R58.1, U20.21, U27.4, U28.2, U29.2, U30.2, U31.2
NET_U20_22: C77.1, R57.2, R59.2, R60.2, U20.11, U20.22
NET_U20_26: C80.1, U20.26
NET_U20_27: C79.1, U20.27
NET_U20_28: C81.1, U20.28
NET_U20_38: R65.1, U20.38
NET_U21_3: U20.2, U21.3
NET_U22_3: U20.37, U22.3
NET_U23_20: R67.1, U23.20
NET_U24_8: R68.1, U24.8
NET_U25_1: R2.1, U25.1, U25.2
PROC_CAN1_RX_TOXCVR: U9.4, U24.5
PROC_CAN1_TX_TOXCVR: U9.1, U24.6
PROC_ETH_CRS_DV_TOXCVR: U3.62, U23.15
PROC_ETH_MDC_TOXCVR: U3.42, U23.17
PROC_ETH_MDIO_TOXCVR: U3.41, U23.18
PROC_ETH_RXD0_TOXCVR: U3.48, U23.13
PROC_ETH_RXD1_TOXCVR: U3.47, U23.11
PROC_ETH_TXD0_TOXCVR: U3.57, U23.12
PROC_ETH_TXD1_TOXCVR: U3.58, U23.16
PROC_ETH_TX_EN_TOXCVR: U3.56, U23.14
PROC_FMC_A16: U1.N10, U8.D4
PROC_FMC_A17: U1.M10, U8.C11
PROC_FMC_A18: U1.M11, U8.D10
PROC_FMC_A19: U1.A2, U8.C10
PROC_FMC_A20: U1.A1, U8.D5
PROC_FMC_A21: U1.B1, U8.C4
PROC_FMC_A22: U1.B2, U8.C12
PROC_FMC_A23: U1.A3, U8.D7
PROC_FMC_CLK: U1.C11, U8.C6
PROC_FMC_D0: U1.L12, U8.F3
PROC_FMC_D1: U1.K13, U8.F4
PROC_FMC_D2: U1.B12, U8.E6
PROC_FMC_D3: U1.C12, U8.E7
PROC_FMC_D4: U1.R8, U8.F8
PROC_FMC_D5: U1.N9, U8.F9
PROC_FMC_D6: U1.P9, U8.E10
PROC_FMC_D7: U1.R9, U8.E11
PROC_FMC_D8: U1.P10, U8.E4
PROC_FMC_D9: U1.R10, U8.E5
PROC_FMC_D10: U1.R12, U8.F6
PROC_FMC_D11: U1.P11, U8.F7
PROC_FMC_D12: U1.R11, U8.E8
PROC_FMC_D13: U1.L15, U8.E9
PROC_FMC_D14: U1.L14, U8.F11
PROC_FMC_D15: U1.K15, U8.F12
PROC_FMC_NE2: R41.1, U1.D9, U8.D11
PROC_FMC_NL: U1.B5, U8.D6
PROC_FMC_NOE: R43.1, U1.D11, U8.E12
PROC_FMC_NWAIT: R40.1, U1.B11, U8.C3
PROC_FMC_NWE: R42.1, U1.C10, U8.C8
PROC_SYS_JTCK_SWCLK: R36.1, U1.A14, U5.9
PROC_SYS_JTDI: R34.1, U1.A13, U5.5
PROC_SYS_JTDO_SWO: U1.A10, U5.13
PROC_SYS_JTMS_SWDIO: R35.1, U1.A15, U5.7
PROC_SYS_JTRST: R33.1, U1.A9, U5.3
PROC_UART4_CTS: U1.R5, U6.13
PROC_UART4_RTS: U1.R14, U6.15
PROC_UART4_RX: U1.C15, U6.16
PROC_UART4_TX: U1.B14, U6.14
RST_OUT_U5_SRESET_B: R37.1, U5.15, U27.1
VCC_14V8: C78.1, C82.1, C83.1, J1.1, R66.2, U20.23, U21.1, U21.2, U21.6, U21.7, U22.1, U22.2, U22.6, U22.7
VCC_S1_14V8: C62.1, C69.1, C70.1, C72.1, R46.2, R51.2, U16.4, U17.7, U17.13, U17.14, U18.4, U21.4, U21.5
VCC_S2_14V8: C75.1, R54.2, U19.4, U22.4, U22.5
VCC_TIER1_1V2: C27.1, C63.1, R47.1, U1.L11, U16.5
VCC_TIER1_1V8: C1.1, C2.1, C3.1, C4.1, C5.1, C6.1, C7.1, C8.1, C9.1, C10.1, C11.1, C12.1, C13.1, C14.1, C15.1, C16.1, C17.1, C18.1, C19.1, C20.1, C21.1, C22.1, C26.1, C47.1, C51.1, C52.1, C53.1, C54.1, C55.1, C56.1, C67.1, C68.1, C86.1, C87.1, C90.1, C91.1, C92.1, C93.1, C94.1, C95.1, C96.1, F1.2, I1.1, I2.2, R8.2, R9.2, R16.2, R17.2, R33.2, R34.2, R35.2, R36.2, R37.2, R39.2, R40.2, R41.2, R42.2, R43.2, R49.1, U1.C1, U1.E7, U1.E8, U1.E9, U1.E10, U1.F4, U1.F5, U1.F11, U1.G5, U1.H5, U1.H11, U1.J5, U1.J11, U1.K5, U1.K11, U1.L7, U1.L8, U1.L9, U1.L10, U5.1, U6.5, U6.12, U8.C7, U8.D3, U8.F10, U17.1, U23.2, U24.2, U27.5, U28.5, U29.5, U30.5, U31.5
VCC_TIER1_3V3: C25.1, C33.1, C41.1, C42.1, C43.1, C44.1, C45.1, C46.1, C57.1, C58.1, C59.1, C60.1, C73.1, C84.1, C85.1, C88.1, C89.1, R7.2, R10.2, R23.2, R27.2, R52.1, R67.2, R68.2, U1.G11, U2.1, U3.1, U3.3, U3.46, U5.2, U9.3, U13.4, U14.4, U15.1, U15.2, U18.5, U23.19, U24.7
VCC_TIER2_1V2: C76.1, R55.1, U19.5
